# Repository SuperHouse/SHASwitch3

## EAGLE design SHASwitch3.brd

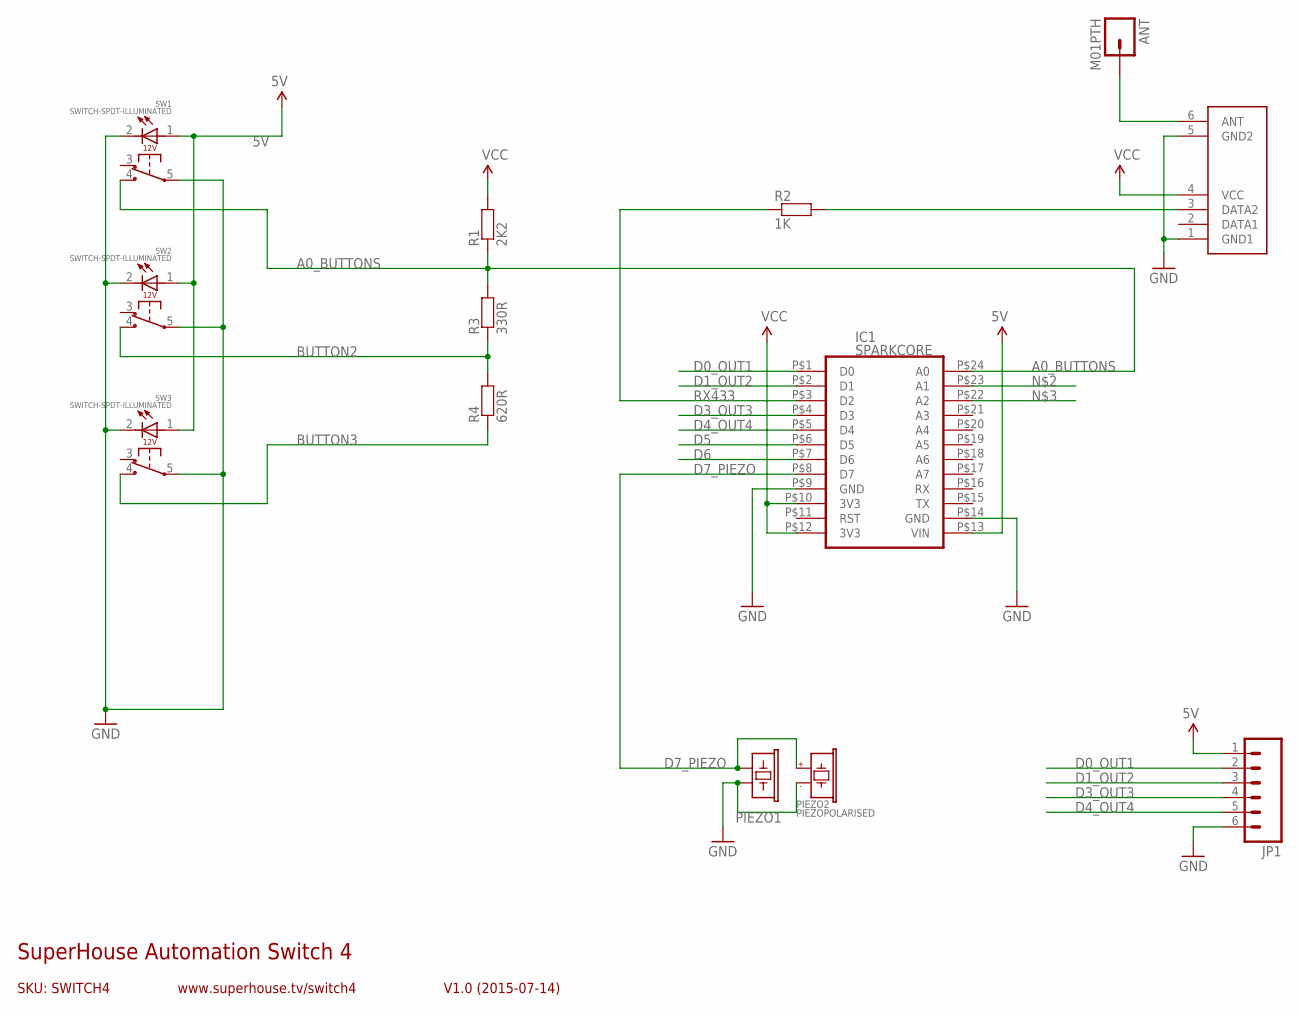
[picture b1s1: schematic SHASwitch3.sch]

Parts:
ANT: M01PTH; 1X01
IC1: SPARKCORE
IC3: RXB1; RX-B1-SHORT-FLAT
JP1: M06SIP; 1X06
PIEZO1: BUZZERSMD12X12; BUZZER-12X12-SMT
PIEZO2: PIEZOPOLARISED; PIEZO12MMWIDEPOLARISED
R1: 2K2; 0603
R2: 1K; 0603
R3: 330R; 0603
R4: 620R; 0603
SW1, SW2, SW3: SWITCH-SPDT-ILLUMINATED

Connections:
5V: IC1.P$13 (VIN), JP1.1, SW1.1 (+), SW2.1 (+), SW3.1 (+)
A0_BUTTONS: IC1.P$24 (A0), R1.1, R3.2, SW1.4 (NO)
BUTTON2: R3.1, R4.2, SW2.4 (NO)
BUTTON3: R4.1, SW3.4 (NO)
D0_OUT1: IC1.P$1 (D0), JP1.2
D1_OUT2: IC1.P$2 (D1), JP1.3
D3_OUT3: IC1.P$4 (D3), JP1.4
D4_OUT4: IC1.P$5 (D4), JP1.5
D5: IC1.P$6 (D5)
D6: IC1.P$7 (D6)
D7_PIEZO: IC1.P$8 (D7), PIEZO1.1, PIEZO2.1 (+)
GND: IC1.P$9 (GND), IC1.P$14 (GND), IC3.1 (GND1), IC3.5 (GND2), JP1.6, PIEZO1.2, PIEZO2.2 (-), SW1.2 (-), SW1.5 (COM), SW2.2 (-), SW2.5 (COM), SW3.2 (-), SW3.5 (COM)
unnamed: ANT.1, IC3.6 (ANT)
unnamed: IC3.3 (DATA2), R2.2
RX433: IC1.P$3 (D2), R2.1
VCC: IC1.P$10 (3V3), IC1.P$12 (3V3), IC3.4 (VCC), R1.2

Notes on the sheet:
SKU: SWITCH4
SuperHouse Automation Switch 4
V1.0 (2015-07-14)
www.superhouse.tv/switch4

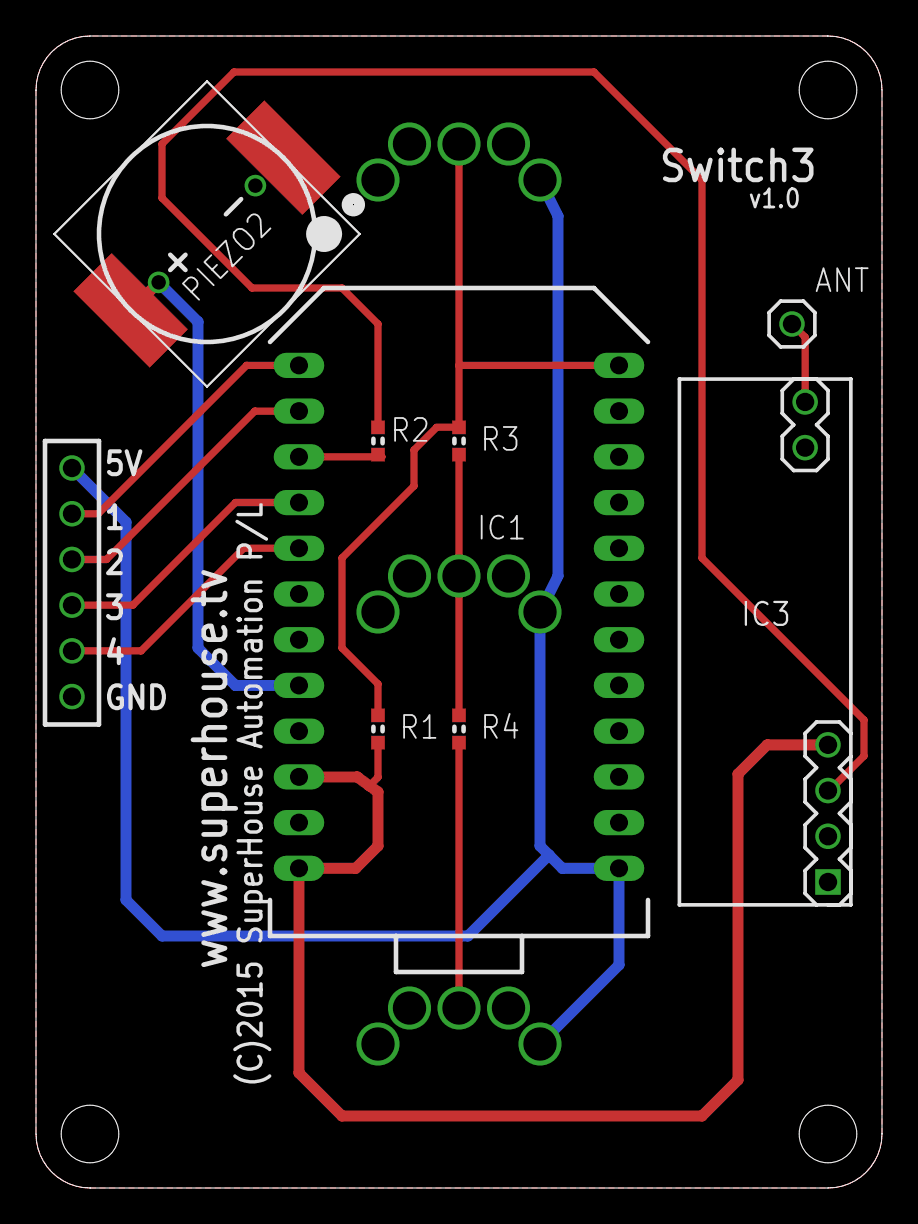
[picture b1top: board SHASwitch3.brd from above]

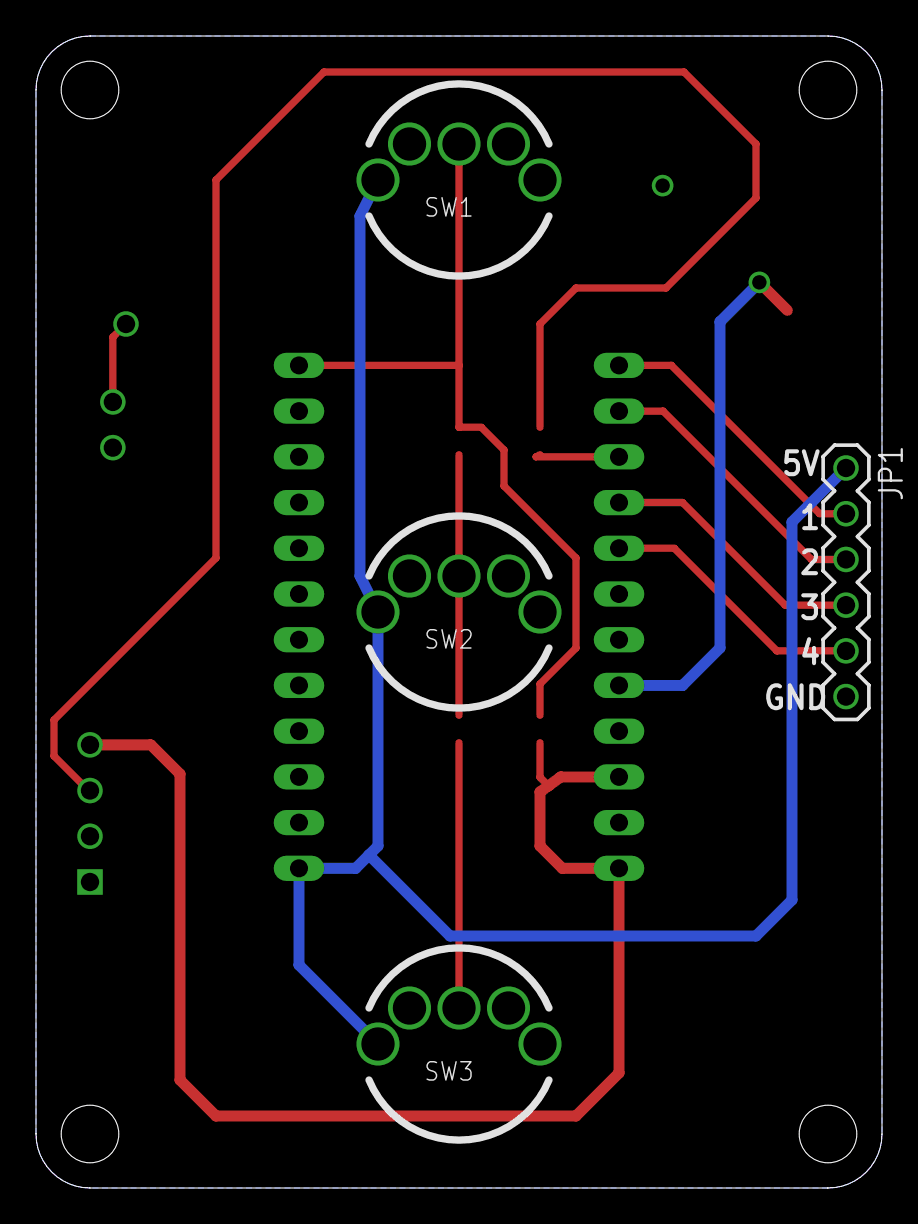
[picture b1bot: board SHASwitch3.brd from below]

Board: 2 copper layers, 47.0 x 64.0 mm, 13 parts (4 on the bottom side), 14 nets.

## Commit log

2019-04-24 Initial project import

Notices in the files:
SHASwitch3.brd:
(C)2015 SuperHouse Automation P/L
parts and their libraries:
freetronics-original: Licensing: CC v3.0 Share-Alike You are welcome to use this library for commercial purposes.
